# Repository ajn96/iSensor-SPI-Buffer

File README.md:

# iSensor SPI Buffer
The iSensor SPI Buffer is a hardware and software solution designed to buffer iSensor IMU data, enabling asynchronous sampling systems (specifically embedded Linux systems) such as the Raspberry Pi, BeagleBone, Nvidia Jetson, etc. to capture IMU data at high sampling rates **with accurate timestamps and** **without data loss**. Output data is provided through a USB Virtual COM port and/or a user SPI port allowing transparent augmentation of an existing IMU interface system.

The firmware runs on an STM32F303 microprocessor to enable full-throughput, buffered IMU data capture with a variety of output data formats. An ADG1611 analog switch IC to enable routing SYNC and DATA READY signals from the host system directly to the IMU. The SPI buffer board is designed to be compatible with all current and future iSensor IMU products. 

A custom PCB was designed to fit the profile and form factor of an ADIS1649x IMU. This profile allows the iSensor SPI Buffer to act as a drop-in solution for existing, high-performance solutions. The buffer interface is designed to mimic the iSensor page convention and SPI settings out-of-the box. 

Additional hardware and software resources are linked below.

[Detailed Register Map](markdown/REGISTER_DEFINITION.md)

[USB CLI Definition](markdown/USB_CLI.md)

[Python USB Interfacing Library](PythonUtil/)

[SD Card Data Logging Scripts](markdown/SD_SCRIPTS.md)

[Firmware Documentation (Doxygen)](https://ajn96.github.io/iSensor-SPI-Buffer/files.html)

[Software Timing Characterization](markdown/TIMING.MD)

[STM32 Processor Pin Map](markdown/PIN_MAP.md)

[Programming Guide](markdown/BUILDING.md)

A video walkthrough and tutorial of the SPI Buffer Board's features is hosted on YouTube. Click on the image below to check it out!

## Hardware Platform

This firmware is designed to operate in the STMicro processor family - specifically the STM32F303 processor. The STM32F303RET6 variant of the processor family was chosen for this application because of its large SRAM and low cost. 

Revision B of the PCB design includes the following features:

- STM32F303RET6 processor (64k SRAM, hardware SPI peripherals, DMA fabric)
- ADG1611 analog switch - used for mapping SYNC and DATA READY signals from the IMU to the buffer board or SPI host
- ADP1706 high-transient linear regulator - used to regulate USB 5V and power both the IMU and buffer board
  - Power supply selection jumper for powering the buffer board & IMU from the 24-pin IMU connector or USB
- USB C expansion port - Provides a USB virtual COM port command line interface to read/write registers and stream IMU data
- SD card slot - Allows IMU data to be captured "headless" without the use of a PC or SPI host
- LEDs - used to indicate buffer state and SPI buffer errors
- 24-pin IMU connectors - used to interface with and pass through IMU and SPI Buffer data to and from a host using SPI
- ADIS1650x footprint - used to enable the evaluation and use of compact iSensor IMUs

The iSensor SPI Buffer was designed to sit between an iSensor IMU and the SPI host without changing any existing PCB designs. 

## Development Environment and Hardware

### Software / IDE

The code contained in this repository was developed using the freely available [STM32 Cube IDE](https://my.st.com/content/my_st_com/en/products/development-tools/software-development-tools/stm32-software-development-tools/stm32-ides/stm32cubeide). A compatible project file is also included in this repository to make getting stared as easy as possible. 

### Hardware

A [TC2030-IDC cable](https://www.tag-connect.com/product/tc2030-idc-6-pin-tag-connect-plug-of-nails-spring-pin-cable-with-legs) must be used to interface with the SWD pads on the Rev B PCB. Development was originally done on an [NUCLEO-F303RE](https://www.st.com/en/evaluation-tools/nucleo-f303re.html) development board. When programming a buffer board, we've continued to use the NUCLEO as the SWD programmer. 

## Linux Driver Support

Support for the SPI Buffer Board in Linux (over SPI) was developed by [spalani7](https://github.com/spalani7). His repository is located  [here](https://github.com/spalani7/adi_imu_driver). For USB interfacing, the included Python library can be utilized for easy integration with any USB capable system.

## Design Requirements and Features

### IMU Register Interface

* "Invisible" SPI pass-through to an iSensor IMU, including modules that implement register pages
* iSensor-SPI-Buffer configuration registers and buffered data acquisition registers will be placed on unassigned IMU pages (Pages 253 - 255)

### Buffered Data Acquisition

* Autonomous IMU data acquisition will be driven by the IMU-generated data ready signal. Data will be stored in the iSensor-SPI-Buffer SRAM until retrieved by a user
* Programmable data request message (MOSI) to be transmitted after each data ready signal. Allows users to customize the register writes, contents, and order
* Programmable data acquisition length after each IMU data ready signal. Allows the user to configure the length of data read back from the IMU
* Programmable data acquisition SPI word size. The default 16-bit length provides support standard register reads, writes, and burst reads on most IMUs

### Configuration Options

* Buffer overflow setting (stop sampling vs delete oldest)
* Data ready input (from IMU) DIO number
* IMU Data ready trigger polarity
* Master SPI (interface between the iSensor-SPI-Buffer firmware and the IMU) 
  * SCLK Frequency
  * Stall time
* Slave SPI (interface between the iSensor-SPI-Buffer firmware and the host processor) 
  * Standard SPI settings (CPOL, CPHA, endianness)

### Buffer Design

* Reading a buffer retrieve register will dequeue data from the buffer data structure to the buffer output registers for retrieval by a user
* The user will can clear the buffer using a control register
* A buffer counter will be added to each buffer for the user to keep track of the state of the buffer. This counter must also be accessible without dequeuing data from buffer
* Using a maximum buffer entry size of 64 bytes, the buffer will provide a minimum of 512 frames of buffering using 32KB SRAM
  * STM32F303 has 80KB of SRAM available, so more than 512 entries may be feasible

## Architecture

### SPI Ports

The iSensor-SPI-Buffer firmware will utilize two hardware SPI ports. One operating as a master (SPI buffer to IMU communication) and the other as a slave (SPI buffer to host)
* The slave SPI port will expose the IMU register interface along with the iSensor-SPI-Buffer configuration registers to the master
* The slave SPI port will support all standard SPI configuration parameters
* The master SPI port will communicate with the IMU using the standard, iSensor SPI protocol
* The master SPI port configuration will be limited to customizing SCLK frequency and stall time

### Program Flow

The iSensor-SPI-Buffer communications interfaces (SPI, SD card logging, USB CLI) are interrupt driven. A main cyclic executive loop handles command execution, interrupt generation, and diagnostics. The cyclic executive flow is shown below:

**User SPI Interrupt**

There will be an ISR to handle user-initiated SPI transactions (slave interface). If the active register page is not one of the SPI buffer pages (253 - 255) all SPI transactions will be forwarded to the IMU downstream. 

SPI transactions will be classified as "read" or "write" by the SPI buffer board the same as the iSensor IMU SPI protocol. A write operation is signaled by setting the MSB of each 16-bit word. The upper 8 bits of the 16-bit transaction contain the register address to be written to as well as the read/write bit. The lower 8 bits of the 16-bit transaction contain the data to be written. 

A single read request transmitted to the SPI buffer on the slave interface will result in *two* SPI transactions sent to the IMU on the master interface. The first transaction sends the register read request to the IMU and the second reads the requested register contents data back from the IMU. The requested IMU register is then loaded into the SPI buffer user SPI transmit buffer so that it is available to the user on the next user SPI transaction.  For write transactions, a single write command will be sent to the IMU. The data resulting from the write transaction is then loaded into the SPI buffer user SPI transmit buffer. Unlike the read operation, a write operation will not automatically generate an additional SPI transaction. The diagram below shows the IMU SPI pass-through process for a register read operation.

**Autonomous Data Capture**

When the currently selected page is 255 (buffer output register page), the iSensor SPI Buffer firmware will begin to monitor a user-specified GPIO interrupt for data ready signals pulses. Once a data ready pulse is detected, the firmware will transmit the data contained in page 254 (buffer transmit data) in the order specified by the user. Data received from the IMU during each 16-bit transaction will be stored in a new buffer entry in the iSensor-SPI-Buffer SRAM. The firmware will use DMA and timer peripherals to perform the SPI transactions with minimal CPU intervention while giving control over the SPI SCLK and stall time. 

The data capture ISR will be triggered by a user-specified GPIO, corresponding to the IMU data ready signal. The data capture ISR will configure a timer peripheral (which drives SPI word transmission timing) to trigger a DMA between memory and SPI. A DMA done ISR will handle cleaning up the DMA transactions and incrementing buffer pointers following a complete data set acquisition from the IMU. If the selected page is changed off page 255, the IMU data ready interrupt data capture functionality will be disabled (can be re-enabled by writing 255 to the page ID register on any page).

**User Interrupt Signaling (to host)**

Each of the four DIO lines from the iSensor-SPI-Buffer to the master device can be configured to operate in one of four modes
* Watermark Interrupt Mode: The selected DIO will go high when a specified number of samples are available to be dequeued. This allows a master device to simply monitor the data ready interrupt signal for a positive edge, and then dequeue a large number of IMU data samples
* Buffer Full Interrupt Mode: The selected DIO will go high when the buffer is full
* Error Interrupt Mode: The selected DIO will go high when an error is detected and flagged in the STATUS register
* Pin Pass-Through Mode: The DIO output from the IMU (e.g. a data ready signal or sync signal) will be directly connected to the master device, using an ADG1611 switch. When a DIO is configured in pin pass-through mode it cannot be used for interrupt signaling

The state of each interrupt signal is checked and updated on each iteration of the main cyclic executive loop. This ensures quick response time to changes in the buffer state while maintaining a simple program flow.

**Command Execution**

* When a write is issued the USER_COMMAND register, a COMMAND flag will be set and processed by the cyclic executive loop
* While a command is being executed, the user SPI port will be disabled, and any interrupt lines (data ready or buffer full) will be brought low

### Register Interface

* Configuration registers for iSensor SPI buffer available on page 253
* The data acquisition write data registers (data to transmit per data ready) available on page 254
* Buffer output data registers on page 255
* Volatile output registers available on page 252

## Recovering From a Bad SPI Configuration

This buffer firmware includes a feature that allows the host SPI peripheral on the buffer board to be reconfigured to suit the host's needs. Because of this, it's possible to lock yourself out of the buffer board. A bad SPI configuration will usually look like the buffer board is returning the same value repeatedly for all registers. Note that the buffer board returning 0xFFFF or 0x0000 could be caused by other issues (no power to the buffer board, bad connection to the IMU, etc.) A bad SPI configuration will look similar to the image below.

Recovering from a bad configuration requires using the USB CLI to communicate with the buffer board's firmware. While not mandatory, we recommend changing the jumper on the buffer board to USB power mode. The jumper just needs to be repositioned as shown below. 

Using a terminal program such as [TeraTerm](https://ttssh2.osdn.jp/index.html.en) or [PuTTY](https://www.chiark.greenend.org.uk/~sgtatham/putty/) in Windows, connect to the board using the enumerated COM port. The virtual USB port will automatically detect the host serial settings, so additional configuration is usually unnecessary. 

Once connected to the CLI, you can verify that the board is communicating correctly by typing `help` into the console. You should see a message like the one shown below.

After you've verified that the CLI is working correctly, type the following command, followed by a carriage return.

`freset`

This will execute a factory reset command followed by a flash update command. The board should now be reset to SPI Mode 3 with CS active low. The default register settings will have also been committed to flash, so they should persist throughout reboots. 

"The SPI who loved me" - PK

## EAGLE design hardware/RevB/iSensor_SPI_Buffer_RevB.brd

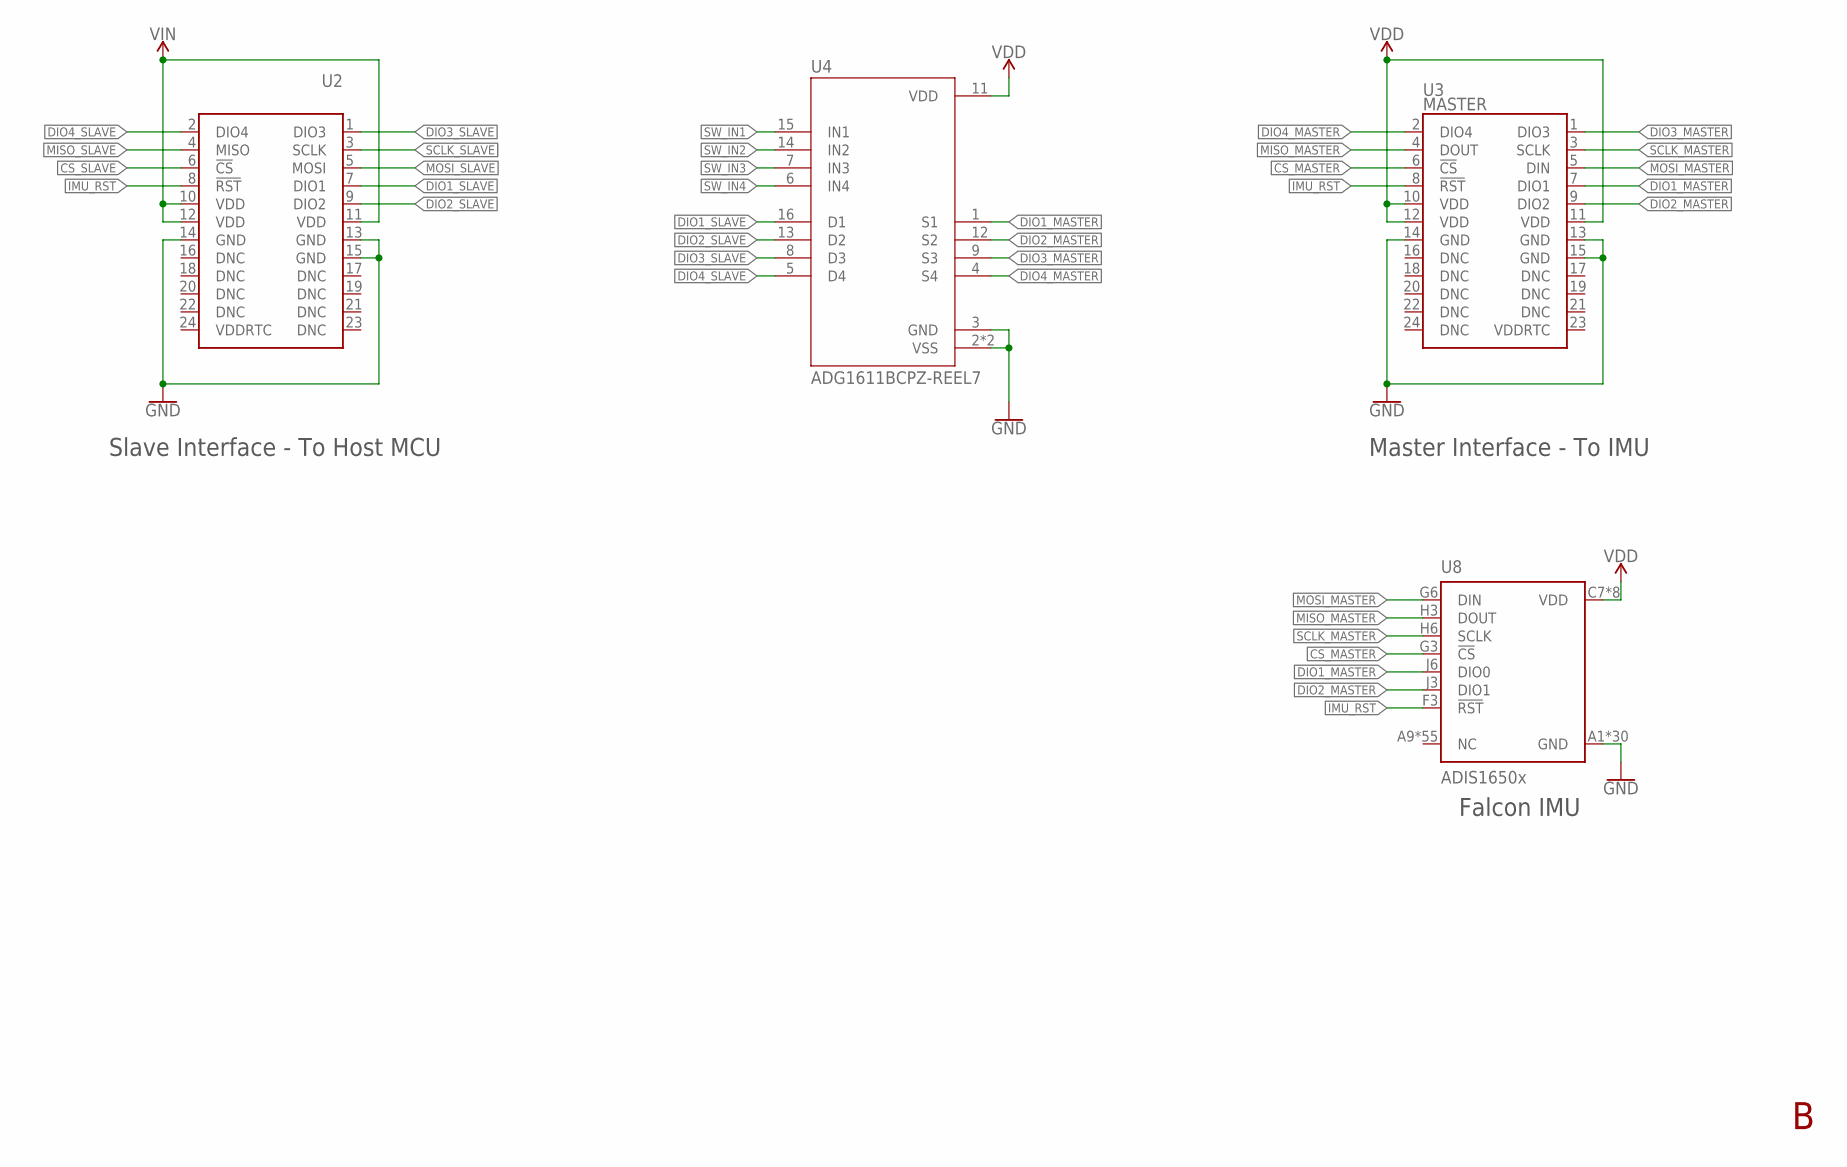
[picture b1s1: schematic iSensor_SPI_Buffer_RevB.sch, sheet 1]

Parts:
U2: MW-12-03-H-D-130-112
U3: MASTER; ADIS1648X
U4: ADG1611BCPZ-REEL7; QFN65P400X400X80-17N
U8: ADIS1650x; ADIS1650X

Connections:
CS_MASTER: U3.6 (!CS), U8.G3 (!CS); also elsewhere on the board
CS_SLAVE: U2.6 (!CS); also elsewhere on the board
DIO1_MASTER: U3.7 (DIO1), U4.1 (S1), U8.J6 (DIO0); also elsewhere on the board
DIO1_SLAVE: U2.7 (DIO1), U4.16 (D1); also elsewhere on the board
DIO2_MASTER: U3.9 (DIO2), U4.12 (S2), U8.J3 (DIO1); also elsewhere on the board
DIO2_SLAVE: U2.9 (DIO2), U4.13 (D2); also elsewhere on the board
DIO3_MASTER: U3.1 (DIO3), U4.9 (S3); also elsewhere on the board
DIO3_SLAVE: U2.1 (DIO3), U4.8 (D3); also elsewhere on the board
DIO4_MASTER: U3.2 (DIO4), U4.4 (S4); also elsewhere on the board
DIO4_SLAVE: U2.2 (DIO4), U4.5 (D4); also elsewhere on the board
GND: U2.13 (GND), U2.14 (GND), U2.15 (GND), U3.13 (GND), U3.14 (GND), U3.15 (GND), U4.2 (VSS), U4.3 (GND), U4.17 (VSS), U8.A1 (GND), U8.A2 (GND), U8.A3 (GND), U8.A4 (GND), U8.A5 (GND), U8.A6 (GND), U8.A7 (GND), U8.A8 (GND), U8.B3 (GND), U8.B4 (GND), U8.B5 (GND), U8.B6 (GND), U8.C2 (GND), U8.C6 (GND), U8.D3 (GND), U8.E2 (GND), U8.E6 (GND), U8.E7 (GND), U8.F1 (GND), U8.F5 (GND), U8.F6 (GND), U8.F8 (GND), U8.G2 (GND), U8.G7 (GND), U8.H8 (GND), U8.J2 (GND), U8.J7 (GND), U8.K1 (GND), U8.K3 (GND), U8.K8 (GND); also elsewhere on the board
IMU_RST: U2.8 (!RST), U3.8 (!RST), U8.F3 (!RST)
MISO_MASTER: U3.4 (DOUT), U8.H3 (DOUT); also elsewhere on the board
MISO_SLAVE: U2.4 (MISO); also elsewhere on the board
MOSI_MASTER: U3.5 (DIN), U8.G6 (DIN); also elsewhere on the board
MOSI_SLAVE: U2.5 (MOSI); also elsewhere on the board
SCLK_MASTER: U3.3 (SCLK), U8.H6 (SCLK); also elsewhere on the board
SCLK_SLAVE: U2.3 (SCLK); also elsewhere on the board
SW_IN1: U4.15 (IN1); also elsewhere on the board
SW_IN2: U4.14 (IN2); also elsewhere on the board
SW_IN3: U4.7 (IN3); also elsewhere on the board
SW_IN4: U4.6 (IN4); also elsewhere on the board
VDD: U3.10 (VDD), U3.11 (VDD), U3.12 (VDD), U4.11 (VDD), U8.C7 (VDD), U8.D6 (VDD), U8.E3 (VDD), U8.G1 (VDD), U8.H1 (VDD), U8.J4 (VDD), U8.J5 (VDD), U8.K6 (VDD); also elsewhere on the board
VIN: U2.10 (VDD), U2.11 (VDD), U2.12 (VDD); also elsewhere on the board

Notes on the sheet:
Slave Interface - To Host MCU
Master Interface - To IMU
Falcon IMU

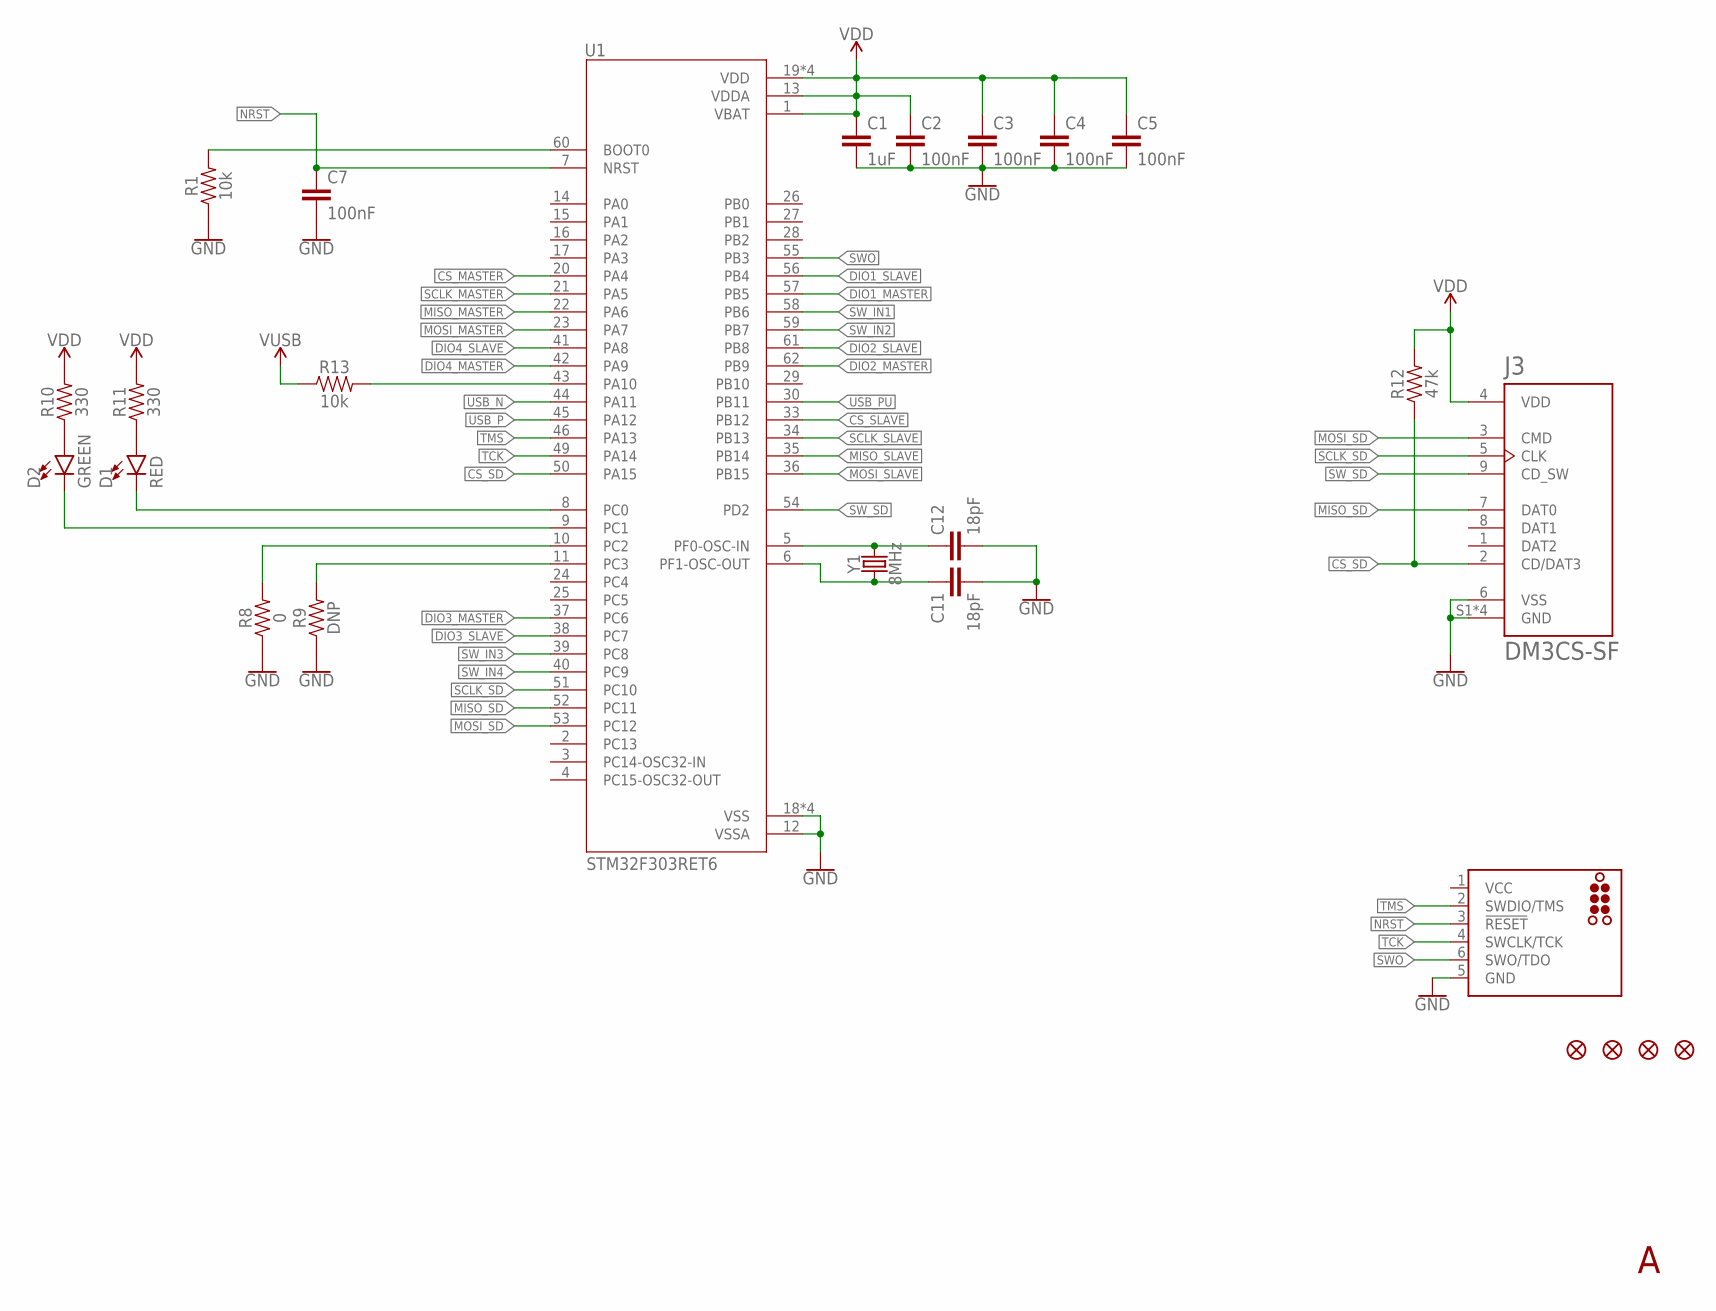
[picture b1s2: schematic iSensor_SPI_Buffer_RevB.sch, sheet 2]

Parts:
C1: 1uF; 0603
C2, C3, C4, C5, C7: 100nF; 0603
C11, C12: 18pF; 0402
D1: RED; LED-0603
D2: GREEN; LED-0603
FD1, FD2, FD3, FD4: FIDUCIAL1X2; FIDUCIAL-1X2
J1: TC2030_SWD-MCP; TC2030-MCP
J3: DM3CS-SF; HRS_DM3CS-SF
R1, R13: 10k; 0402
R8: 0; 0402
R9: DNP; 0402
R10, R11: 330; 0402
R12: 47k; 0402
U1: STM32F303RET6; QFP50P1200X1200X160-64N
Y1: 8MHz; CRYSTAL-SMD-5X3.2-4PAD

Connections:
CS_MASTER: U1.20 (PA4); also elsewhere on the board
CS_SD: J3.2 (CD/DAT3), R12.1, U1.50 (PA15)
CS_SLAVE: U1.33 (PB12); also elsewhere on the board
DIO1_MASTER: U1.57 (PB5); also elsewhere on the board
DIO1_SLAVE: U1.56 (PB4); also elsewhere on the board
DIO2_MASTER: U1.62 (PB9); also elsewhere on the board
DIO2_SLAVE: U1.61 (PB8); also elsewhere on the board
DIO3_MASTER: U1.37 (PC6); also elsewhere on the board
DIO3_SLAVE: U1.38 (PC7); also elsewhere on the board
DIO4_MASTER: U1.42 (PA9); also elsewhere on the board
DIO4_SLAVE: U1.41 (PA8); also elsewhere on the board
GND: C1.2, C2.2, C3.2, C4.2, C5.2, C7.2, C11.2, C12.2, J1.5 (GND), J3.6 (VSS), J3.S1 (GND), J3.S2 (GND), J3.S3 (GND), J3.S5 (GND), R1.1, R8.1, R9.1, U1.12 (VSSA), U1.18 (VSS), U1.31 (VSS), U1.47 (VSS), U1.63 (VSS); also elsewhere on the board
MISO_MASTER: U1.22 (PA6); also elsewhere on the board
MISO_SD: J3.7 (DAT0), U1.52 (PC11)
MISO_SLAVE: U1.35 (PB14); also elsewhere on the board
MOSI_MASTER: U1.23 (PA7); also elsewhere on the board
MOSI_SD: J3.3 (CMD), U1.53 (PC12)
MOSI_SLAVE: U1.36 (PB15); also elsewhere on the board
unnamed: R1.2, U1.60 (BOOT0)
unnamed: D1.C, U1.8 (PC0)
unnamed: D2.C, U1.9 (PC1)
unnamed: R8.2, U1.10 (PC2)
unnamed: R9.2, U1.11 (PC3)
unnamed: D2.A, R10.1
unnamed: D1.A, R11.1
unnamed: R13.2, U1.43 (PA10)
unnamed: C11.1, U1.6 (PF1-OSC-OUT), Y1.1
unnamed: C12.1, U1.5 (PF0-OSC-IN), Y1.3 (2)
NRST: C7.1, J1.3 (!RESET), U1.7 (NRST)
SCLK_MASTER: U1.21 (PA5); also elsewhere on the board
SCLK_SD: J3.5 (CLK), U1.51 (PC10)
SCLK_SLAVE: U1.34 (PB13); also elsewhere on the board
SWO: J1.6 (SWO/TDO), U1.55 (PB3)
SW_IN1: U1.58 (PB6); also elsewhere on the board
SW_IN2: U1.59 (PB7); also elsewhere on the board
SW_IN3: U1.39 (PC8); also elsewhere on the board
SW_IN4: U1.40 (PC9); also elsewhere on the board
SW_SD: J3.9 (CD_SW), U1.54 (PD2)
TCK: J1.4 (SWCLK/TCK), U1.49 (PA14)
TMS: J1.2 (SWDIO/TMS), U1.46 (PA13)
USB_N: U1.44 (PA11); also elsewhere on the board
USB_P: U1.45 (PA12); also elsewhere on the board
USB_PU: U1.30 (PB11); also elsewhere on the board
VDD: C1.1, C2.1, C3.1, C4.1, C5.1, J3.4 (VDD), R10.2, R11.2, R12.2, U1.1 (VBAT), U1.13 (VDDA), U1.19 (VDD), U1.32 (VDD), U1.48 (VDD), U1.64 (VDD); also elsewhere on the board
V_USB: R13.1; also elsewhere on the board

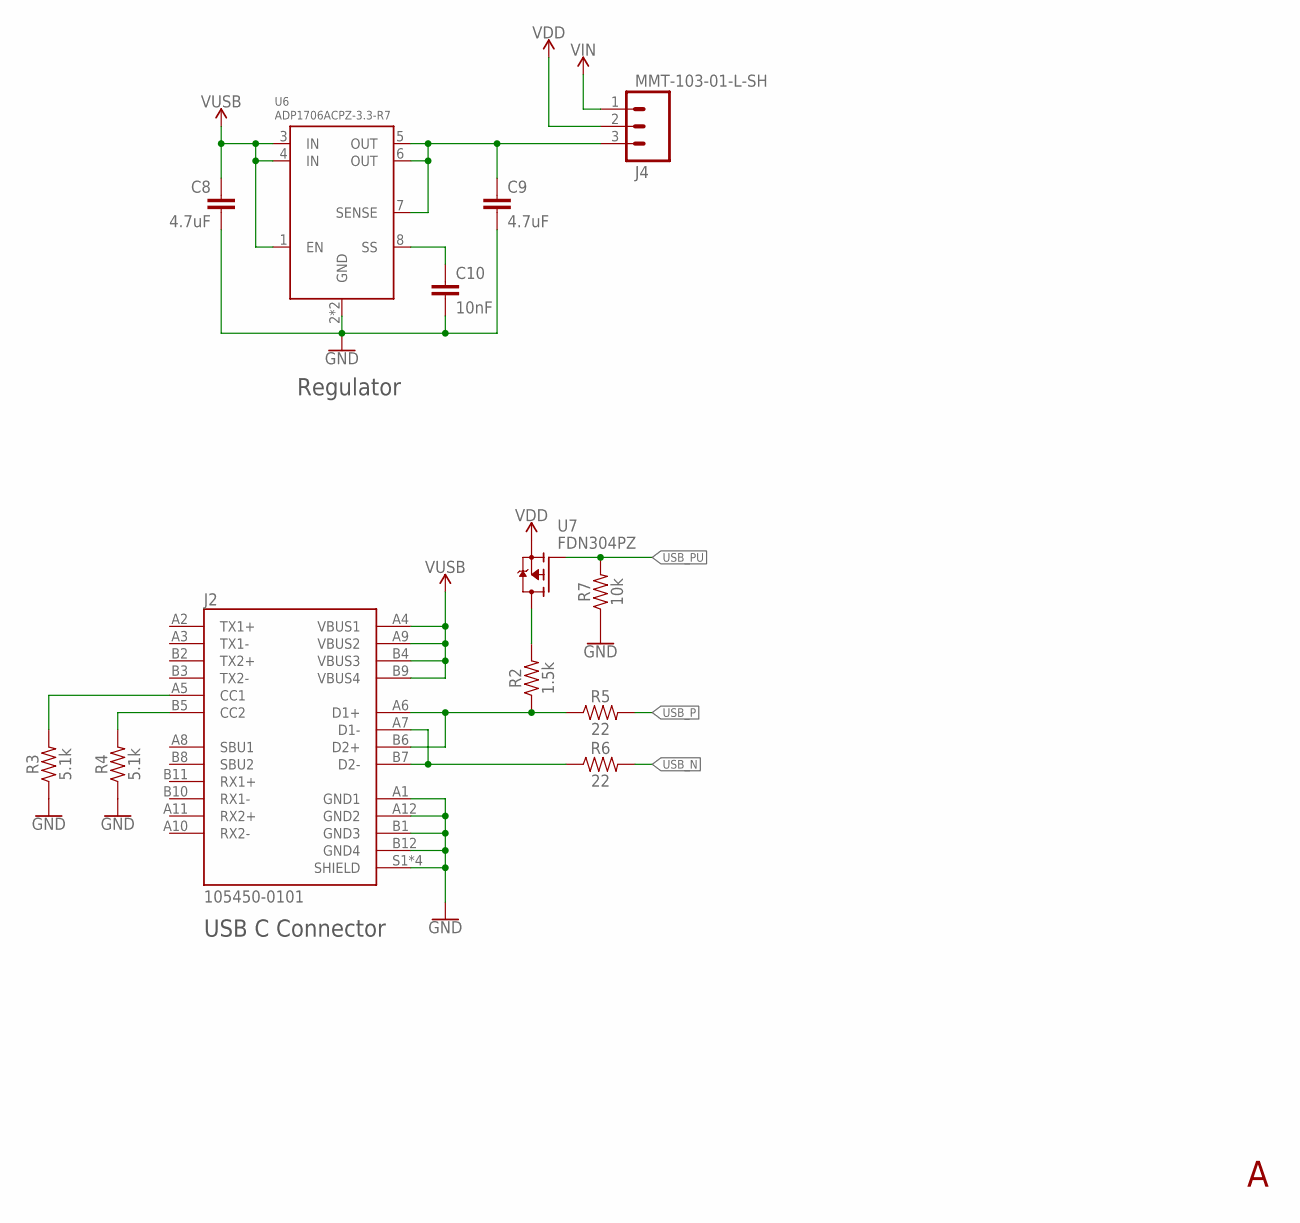
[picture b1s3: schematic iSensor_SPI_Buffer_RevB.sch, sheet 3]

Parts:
C8, C9: 4.7uF; 0805
C10: 10nF; 0603
J2: 105450-0101; MOLEX_105450-0101
J4: MMT-103-01-L-SH; SAMTEC-MMT-103-01-X-SH
R2: 1.5k; 0402
R3, R4: 5.1k; 0402
R5, R6: 22; 0402
R7: 10k; 0402
U6: ADP1706ACPZ-3.3-R7; DFN300X300X90-9N
U7: FDN304PZ; SOT23

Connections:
GND: C8.2, C9.2, C10.2, J2.A1 (GND1), J2.A12 (GND2), J2.B1 (GND3), J2.B12 (GND4), J2.S1 (SHIELD), J2.S2 (SHIELD), J2.S3 (SHIELD), J2.S4 (SHIELD), R3.1, R4.1, R7.1, U6.2 (GND), U6.9 (GND); also elsewhere on the board
unnamed: J2.A5 (CC1), R3.2
unnamed: J2.B5 (CC2), R4.2
unnamed: C9.1, J4.3, U6.5 (OUT), U6.6 (OUT), U6.7 (SENSE)
unnamed: R2.2, U7.3 (D)
unnamed: C10.1, U6.8 (SS)
USB+_N: J2.A7 (D1-), J2.B7 (D2-), R6.1
USB+_P: J2.A6 (D1+), J2.B6 (D2+), R2.1, R5.1
USB_N: R6.2; also elsewhere on the board
USB_P: R5.2; also elsewhere on the board
USB_PU: R7.2, U7.1 (G); also elsewhere on the board
VDD: J4.2, U7.2 (S); also elsewhere on the board
VIN: J4.1; also elsewhere on the board
V_USB: C8.1, J2.A4 (VBUS1), J2.A9 (VBUS2), J2.B4 (VBUS3), J2.B9 (VBUS4), U6.1 (EN), U6.3 (IN), U6.4 (IN); also elsewhere on the board

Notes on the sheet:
USB C Connector
Regulator

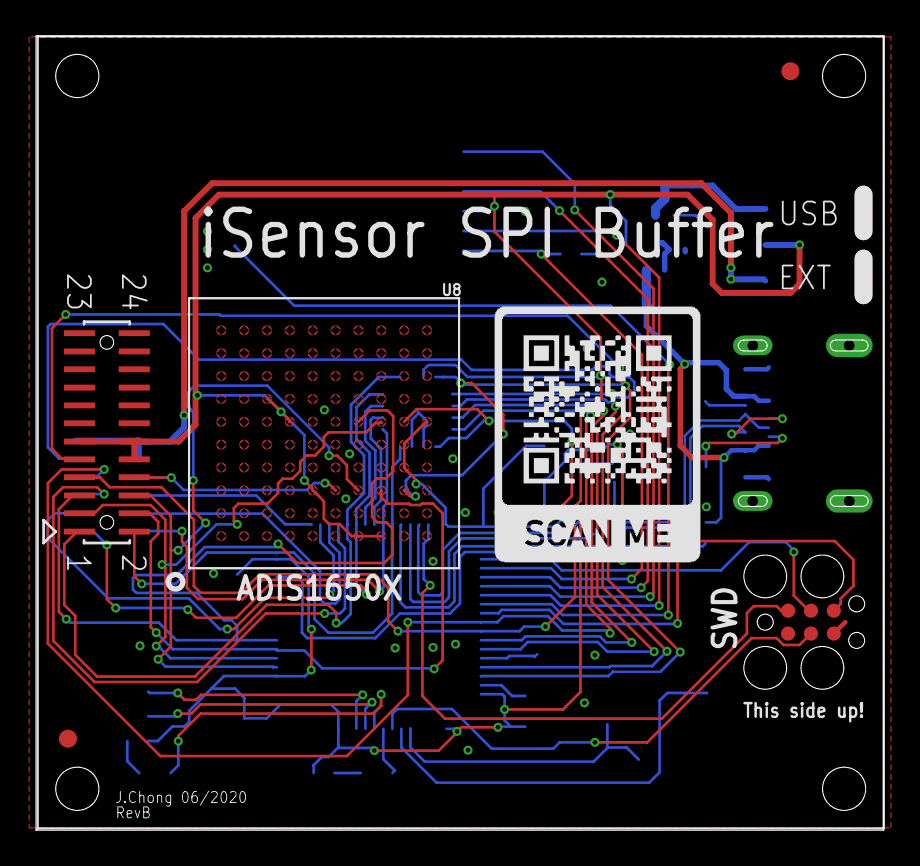
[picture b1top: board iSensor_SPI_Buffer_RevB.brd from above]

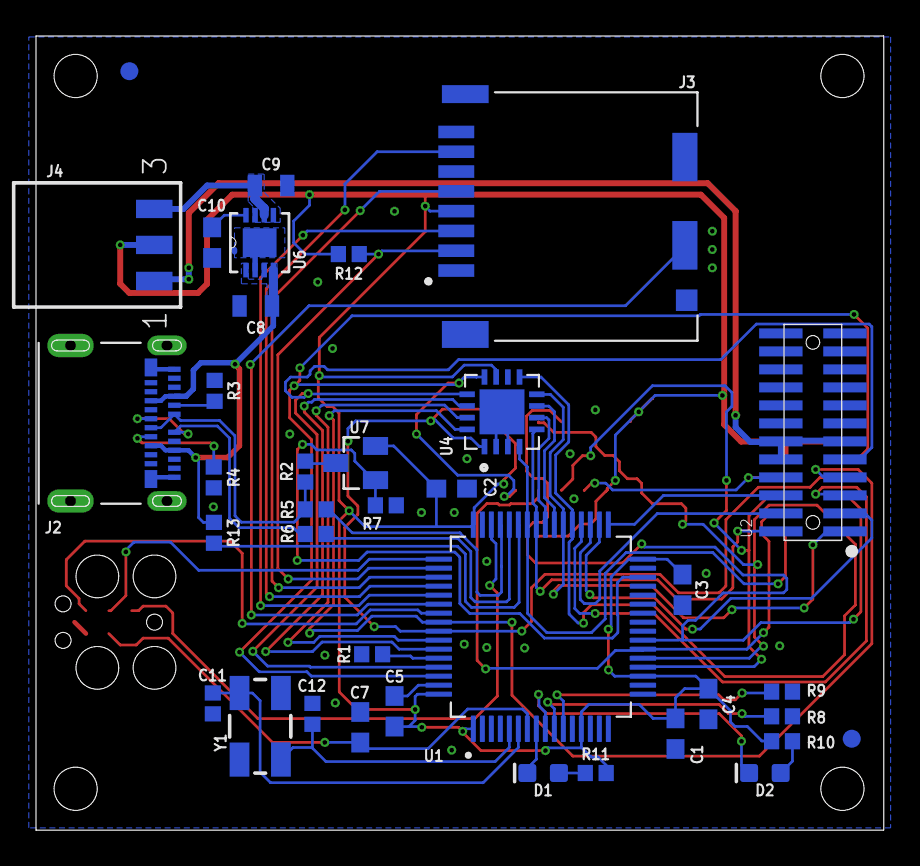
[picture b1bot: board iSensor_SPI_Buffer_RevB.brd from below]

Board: 2 copper layers, 47.1 x 44.1 mm, 42 parts (37 on the bottom side), 54 nets.

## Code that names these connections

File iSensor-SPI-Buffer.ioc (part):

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Mcu.Name=STM32F303R(D-E)Tx
Mcu.Package=LQFP64
Mcu.UserName=STM32F303RETx
PA11.Mode=Device
PA11.Signal=USB_DM
PA12.Mode=Device
PA12.Signal=USB_DP
PA13.Signal=SYS_JTMS-SWDIO
PA14.Signal=SYS_JTCK-SWCLK
PA15.Mode=NSS_Signal_Hard_Output
PA15.Signal=SPI3_NSS
PA4.Signal=S_TIM3_CH2
PA5.Mode=Full_Duplex_Master
PA5.Signal=SPI1_SCK
PA6.Mode=Full_Duplex_Master
PA6.Signal=SPI1_MISO
PA7.Mode=Full_Duplex_Master
PA7.Signal=SPI1_MOSI
PA8.Signal=GPIO_Output
PA9.Signal=GPIO_Input
PB12.Mode=NSS_Signal_Hard_Input
PB12.Signal=SPI2_NSS
PB13.Mode=Full_Duplex_Slave
PB13.Signal=SPI2_SCK
PB14.Mode=Full_Duplex_Slave
PB14.Signal=SPI2_MISO
PB15.Mode=Full_Duplex_Slave
PB15.Signal=SPI2_MOSI
PB3.Signal=SYS_JTDO-TRACESWO
PB4.Signal=GPIO_Output
PB5.Signal=GPXTI5
PB6.Signal=GPIO_Output
PB7.Signal=GPIO_Output
PB8.Signal=GPIO_Output
PB9.Signal=GPIO_Input
PC10.Mode=Full_Duplex_Master
PC10.Signal=SPI3_SCK
PC11.Mode=Full_Duplex_Master
PC11.Signal=SPI3_MISO
PC12.Mode=Full_Duplex_Master
PC12.Signal=SPI3_MOSI
PC6.Signal=GPIO_Input
PC7.Signal=GPIO_Output
PC8.Signal=GPIO_Output
PC9.Signal=GPIO_Output
RCC.HSE_VALUE=8000000
RCC.SYSCLKFreq_VALUE=72000000
RCC.SYSCLKSourceVirtual=RCC_SYSCLKSOURCE_PLLCLK
board=custom

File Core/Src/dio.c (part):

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		g_regs[SYNC_FREQ_REG] = 1;
	}

	/* Pin in question is PB8. Can mux to timer16, CH1. */

	/**TIM16 GPIO Configuration PB8 */
	GPIO_InitStruct.Pin = GPIO_PIN_8;
	GPIO_InitStruct.Mode = GPIO_MODE_AF_PP;
	GPIO_InitStruct.Pull = GPIO_NOPULL;
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	GPIO_InitStruct.Pull = GPIO_NOPULL;
	GPIO_InitStruct.Speed = GPIO_SPEED_FREQ_HIGH;

	/* DIO1 master (PB5) */
	HAL_GPIO_DeInit(GPIOB, GPIO_PIN_5);
	GPIO_InitStruct.Pin = GPIO_PIN_5;
	if(config & 0x1)
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	/* Apply settings */
	HAL_GPIO_Init(GPIOB, &GPIO_InitStruct);

	/* DIO2 master (PB9) */
	HAL_GPIO_DeInit(GPIOB, GPIO_PIN_9);
	GPIO_InitStruct.Pin = GPIO_PIN_9;
	if(config & 0x2)
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	/* Apply settings */
	HAL_GPIO_Init(GPIOB, &GPIO_InitStruct);

	/* DIO3 master (PC6) */
	HAL_GPIO_DeInit(GPIOC, GPIO_PIN_6);
	GPIO_InitStruct.Pin = GPIO_PIN_6;
	if(config & 0x4)
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	/* Apply settings */
	HAL_GPIO_Init(GPIOC, &GPIO_InitStruct);

	/* DIO4 master (PA9) */
	HAL_GPIO_DeInit(GPIOA, GPIO_PIN_9);
	GPIO_InitStruct.Pin = GPIO_PIN_9;
	if(config & 0x8)
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  * General procedure is as follows:
  *
  * passPins
  * Set SW_IN1 - SW_IN4 output values based on passPins. These act as inputs
  * to the ADG1611 analog switch. For each bit set in passPins, configure the
  * corresponding DIOx_Slave signal as an input (tristate). Only perform this
  * configuration if the pin is not currently acting as a PPS input
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
	/* All SW_INx pins are driven as outputs */

	/* SW_IN1 (PB6) */
	if(g_pinConfig.passPins & 0x1)
		GPIOB->ODR &= ~GPIO_PIN_6;
	else
		GPIOB->ODR |= GPIO_PIN_6;

	/* SW_IN2 (PB7) */
	if(g_pinConfig.passPins & 0x2)
		GPIOB->ODR &= ~GPIO_PIN_7;
	else
		GPIOB->ODR |= GPIO_PIN_7;

	/* SW_IN3 (PC8) */
	if(g_pinConfig.passPins & 0x4)
		GPIOC->ODR &= ~GPIO_PIN_8;
	else
		GPIOC->ODR |= GPIO_PIN_8;

	/* SW_IN4 (PC9) */
	if(g_pinConfig.passPins & 0x8)
		GPIOC->ODR &= ~GPIO_PIN_9;
	else
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
	/* For each DIOx_Slave pin, set as output if used as interrupt source. Set as input if used as pass pin (and not PPS) */

	/* DIO1_Slave (PB4) */
	if((g_pinConfig.watermarkPins & 0x1) || (g_pinConfig.overflowPins & 0x1) || (g_pinConfig.errorPins & 0x1))
	{
		HAL_GPIO_DeInit(GPIOB, GPIO_PIN_4);
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		HAL_GPIO_Init(GPIOB, &GPIO_InitStruct);
	}

	/* DIO2_Slave (PB8) */
	if((g_pinConfig.watermarkPins & 0x2) || (g_pinConfig.overflowPins & 0x2) || (g_pinConfig.errorPins & 0x2))
	{
		HAL_GPIO_DeInit(GPIOB, GPIO_PIN_8);
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		HAL_GPIO_Init(GPIOB, &GPIO_InitStruct);
	}

	/* DIO3_Slave (PC7) */
	if((g_pinConfig.watermarkPins & 0x4) || (g_pinConfig.overflowPins & 0x4) || (g_pinConfig.errorPins & 0x4))
	{
		GPIO_InitStruct.Mode = GPIO_MODE_OUTPUT_PP;
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		HAL_GPIO_Init(GPIOC, &GPIO_InitStruct);
	}

	/* DIO4_Slave (PA8) */
	if((g_pinConfig.watermarkPins & 0x8) || (g_pinConfig.overflowPins & 0x8) || (g_pinConfig.errorPins & 0x8))
	{
		HAL_GPIO_DeInit(GPIOA, GPIO_PIN_8);
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
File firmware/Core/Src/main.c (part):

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	/*Configure GPIO port C pin Output Level */
	HAL_GPIO_WritePin(GPIOC, GPIO_PIN_0|GPIO_PIN_1|GPIO_PIN_8|GPIO_PIN_9, GPIO_PIN_RESET);

	/*Configure GPIO port A input pin : PA8 PA9 */
	GPIO_InitStruct.Pin = GPIO_PIN_8|GPIO_PIN_9;
	GPIO_InitStruct.Mode = GPIO_MODE_INPUT;
	GPIO_InitStruct.Pull = GPIO_NOPULL;
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	GPIO_InitStruct.Speed = GPIO_SPEED_FREQ_HIGH;
	HAL_GPIO_Init(GPIOB, &GPIO_InitStruct);

	/*Configure GPIO port B input pins : PB4 PB5 PB8 PB9 */
	GPIO_InitStruct.Pin = GPIO_PIN_4|GPIO_PIN_5|GPIO_PIN_8|GPIO_PIN_9;
	GPIO_InitStruct.Mode = GPIO_MODE_INPUT;
	GPIO_InitStruct.Pull = GPIO_NOPULL;
	HAL_GPIO_Init(GPIOB, &GPIO_InitStruct);

	/*Configure GPIO port B output pins : PB6 PB7 (Switch control) */
	GPIO_InitStruct.Pin = GPIO_PIN_6|GPIO_PIN_7;
	GPIO_InitStruct.Mode = GPIO_MODE_OUTPUT_PP;
	GPIO_InitStruct.Pull = GPIO_NOPULL;
	GPIO_InitStruct.Speed = GPIO_SPEED_FREQ_HIGH;
	HAL_GPIO_Init(GPIOB, &GPIO_InitStruct);

	/*Configure GPIO port C input pins : PC2 PC3 PC6 PC7 */
	GPIO_InitStruct.Pin = GPIO_PIN_2|GPIO_PIN_3|GPIO_PIN_6|GPIO_PIN_7;
	GPIO_InitStruct.Mode = GPIO_MODE_INPUT;
	GPIO_InitStruct.Pull = GPIO_NOPULL;
	HAL_GPIO_Init(GPIOC, &GPIO_InitStruct);

	/*Configure GPIO port C output pins : PC0 PC1 PC8 PC9 (LED, Switch control) */
	GPIO_InitStruct.Pin = GPIO_PIN_0|GPIO_PIN_1|GPIO_PIN_8|GPIO_PIN_9;
	GPIO_InitStruct.Mode = GPIO_MODE_OUTPUT_PP;
	GPIO_InitStruct.Pull = GPIO_NOPULL;
	GPIO_InitStruct.Speed = GPIO_SPEED_FREQ_HIGH;
	HAL_GPIO_Init(GPIOC, &GPIO_InitStruct);

	/**TIM3 GPIO Configuration PA4     ------> TIM3_CH2 */
	GPIO_InitStruct.Pin = GPIO_PIN_4;
	GPIO_InitStruct.Mode = GPIO_MODE_AF_PP;
	GPIO_InitStruct.Pull = GPIO_NOPULL;
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	GPIO_InitStruct.Alternate = GPIO_AF2_TIM3;
	HAL_GPIO_Init(GPIOA, &GPIO_InitStruct);

	/*Configure GPIO port D input pins : PD2 (SD card detect) */
	GPIO_InitStruct.Pin = GPIO_PIN_2;
	GPIO_InitStruct.Mode = GPIO_MODE_INPUT;
	GPIO_InitStruct.Pull = GPIO_NOPULL;
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
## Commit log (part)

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2020-06-27 Renamed register array to g_regs. Starting to refactor to work on variable scope
2020-06-27 More refactoring and cleanup on coding style. Renamed imu_passthrough module to imu spi to be more concise
2020-06-27 Rebuilt firmware documentation
2020-06-27 Reordered status bits
2020-06-27 Updated project file
2020-06-27 Added missing variable reference
2020-06-29 Started CLI implementation
2020-06-29 Implemented basic CLI. Read/write/help working
2020-07-01 Added docs for USB_CONFIG register
2020-07-01 Made it so delim char does not appear on end of line
2020-07-01 Added pictures to USB cli definition
2020-07-05 Updated register info
2020-07-06 Updated CLI images
2020-07-06 Updated regmaps with new registers
2020-07-06 Added UTC timestamp to buffer entry. Removed delta time
2020-07-06 Changed timestamps to be written to buffer word wise
2020-07-06 Fixed buf data base address define
2020-07-06 Updated gitignore
2020-07-06 Command echo is now blocking. Might do something more efficient later
2020-07-07 Fixed bug where LSB first mode wouldnt actually change
2020-07-07 Marked command as volatile
2020-07-07 Added more commenting for missing documentation
2020-07-07 Changed firmware rev to 1.01
2020-07-07 Added generated init code for IMU DMA
2020-07-07 removed unneeded global flags for active interrupt masks
2020-07-07 Started logic for IMU burst data capture
2020-07-09 Changed rev back to 1.0 for re-release
2020-07-09 Changed firmware rev back to 1.1
2020-07-09 Fixed buf_config default, removed status TC test
2020-07-09 Updated the readme to include instructions on changing the spi settings using the USB cli and added a link to the Linux driver repository
2020-07-10 Added bit to USB_CONFIG which allows a user to disable the CLI echo. This is useful when programatically interfacing with Spi buffer CLI (don't have to throw away echoed commands)
2020-07-10 Changed reset command to a factory reset command, freset
2020-07-10 Added HAL code for ADC
2020-07-10 temp reading now produces and scales data. Think the wrong source is set, output values are way off
2020-07-13 Restructured main loop to allow better latency setting interrupts
2020-07-15 Fixed issue where you would sometimes get invalid IMU stall time
2020-07-20 Fixed typo
2020-07-21 Added temp register
2020-07-21 Started working on burst implementation
2020-07-22 Implemented IMU burst data streaming functionality using DMA
2020-07-23 Flush SPI when exiting burst
2020-07-23 Improved documentation for temp sensor module, added temp warning to STATUS
2020-07-23 Added burst regs to regmap
2020-07-24 Initial source commit for script module (USB + CLI)
2020-07-24 Changed firmware rev to 1.3
2020-07-24 Fixed register bit assignments to actually match docs
2020-07-24 Refactored script parse function to be a more maintainable
2020-07-27 Updated timestamp again with a higher sample freq
2020-07-27 Made it so FW_REV is loaded from #define instead of flash
2020-07-28 Reworked user SPI interface to interrupt on rising edge of CS in all modes
2020-07-28 added PPS unlock detection for pps period error of more than 1%
2020-07-28 Added more documentation, cleaned up variable scopes
2020-07-28 Incremented working version number
2020-07-28 Added SD card interface module stubs
2020-07-29 Fixed extra word being placed in SPI Tx FIFO when an overrun error event is generated
2020-07-29 Added handling for new commands
2020-07-29 Moved SPI3 init to SD card module, added outline of functionality
2020-07-29 Continued script execution engine implementation
2020-07-29 Added documentation for SD data logging
2020-08-02 Fixed issue with CS PWM timer configuration making changes take one period to be applied. Now compare register is updated immediately
2020-08-02 Added function to check script autorun. Moved watchdog flag check to after regs are loaded from flash (whoops)
2020-08-02 Changed init order slightly to make behavior more consistent
2020-08-02 Incremented working firmware rev to 1.5
2020-08-05 Updated capture running check to look at DMA count registers
2020-08-05 Added image showing SPI pass through
2020-08-05 Incremented working firmware rev
2020-08-06 Added call to errorhandler which was somehow removed
2020-08-06 Fixed issue where IMU data ready interrupt would be cleared by CS rising edge ISR. Fixed issue where sometimes user SPI would not properly reset before a burst, resulting in a data offset
2020-08-06 Changed working firmware rev to 1.7
2020-08-06 Added function to find vdd value from vrefint measurement
2020-08-07 Added docs for watermark strobe mode
2020-08-07 Updated formatting and regenerated output
2020-08-07 Added BUF_CNT output to burst word 0
2020-08-07 Changed working firmware rev to 1.8:
2020-08-09 Refactored script code to be context aware and just call appropriate USB/SD card handler for tx data. This simplifies handling multi-buffer writes
2020-08-09 Moved stream check to its own function within script module. Is called periodically in main loop
2020-08-10 USB CLI functionality now sits entirely on top of script module for all functionality
2020-08-10 Made functional minimum watermark level for streams 1
2020-08-10 Also masked lowest bit in address
2020-08-10 Fixed potential buffer overflow issue. Reworked blocking USB transmit function call
2020-08-23 Renamed ADC functions
2020-08-23 SD card logging implementation should be done. Still work remaining to debug some misc bugs. Made changes to remove all compiler warnings
2020-08-23 Reworked main state machine to be cleaner
2020-08-23 Compensated the temperature sensor output reading based on the latest measured Vdd voltage
2020-08-23 Added decimation to temp reading to make it less noisey
2020-08-23 Lowered SCLK speed and changed word size from 4bits to 8 bits
2020-08-24 Added two new script info registers - line counter, and error status register
2020-08-24 Added doxygen style comment blocks for all functions
2020-08-24 Updated doxygen
2020-08-24 Made it so VREFINT is sampled prior to temp sensor. This prevents issue where TEMP warning is set in STATUS on startup, due to Vdd register being zero when first temp sensor value is calibrated
2020-09-06 Renamed USB_CONFIG to CLI_CONFIG
2020-09-06 Continued SD card data logging implementation. Script file load now working, program throws error creating result text file however
2020-09-16 Added critical section to buf dequeue to prevent potential issues if interrupted by IRQ
2020-09-21 Added support for PPS input signals at 1Hz, 10Hz, 100Hz, 1KHz
2020-09-21 Updated bit definitions for DIO_INPUT_CONFIG
2020-09-27 Reduced ADC clock freq by 50%, increased temp sensor averaging
2020-09-28 Moved disable data capture to main loop, changed it so enable/disable only occurs on write to addr 0
2020-09-28 Changed delay microseconds function to reset DWT timer
2020-09-28 Made some tweaks to the capture enable/disable process
2020-09-30 Switch spi timeout to use HAL systick
2020-10-01 Fixed issue in SD card disk I/O driver causing buffer overflow by 1 byte
2020-10-01 Reverted so output file is opened in append mode. Fixed bug in SD tx handler
2020-10-01 Updated comments and some of the CLI messages. Added new echo command to enable/disable CLI echo for USB
2020-10-01 Fixed formatting
2020-10-01 Fixed some missing function documentation, updated header file to exclude functions from doxygen output
2020-10-01 Updated docs
2020-10-01 Updated timing meaurement, fixed small issue with factory reset time measure function
2020-10-04 Updated documentation for new commands
2020-10-05 Updated CLI docs and help message
2020-10-05 Reworded help message somewhat
2020-10-05 Made CLI tx handlers return for count of 0, fixed issue where two newlines could be inadvertently inserted
2020-10-09 Added cnt read alias command
2020-10-09 Added iamge for CLI cnt command
2020-10-09 Updated the USB CLI description document
2020-10-09 Added a link to the tutorial in the USB_CLI document
2020-10-09 Added the buffer count read command and added the watermark setting to the cli tutorial
2020-10-09 Started working on bootloader jump function
2020-10-09 Created python file for wrapper around CLI
2020-10-11 Added command bit to automatically set the watermark interrupt level
2020-10-12 Changed scr0 -> btn config
2020-10-17 Tweaked some register descriptions
2020-10-17 Got python api working at a base level
2020-10-17 Started to populate example
2020-10-17 Fleshed out example. Seems to be very performanced limited compared to something like tera-term. Will have to investigate more clever readline implementation
2020-10-17 Added readme for python lib
2020-10-18 Renamed folder, added link to top level readme
2020-10-18 Tweaked python lib
2020-10-18 Stop stream now blocks until stream thread exits. Added getters for temp/voltage and updated examples
2020-10-18 Added image showing windows run for example program
2020-10-20 Started working on figuring out how to force USB re-enum on the PC side
2020-10-22 Added name to files, added test file
2020-10-22 Continued test implementation
2020-10-24 Some pretty major changes here. I added a new feature which allows the buffer board to generate an internal sync clock that can be passed to IMU, or used as buffered capture trigger for testing. Deci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
2020-10-24 Fixed checksum calculation
2020-10-24 Added volatile page 252 for future dev work
2020-10-24 Added page 252 description
2020-10-25 Added class to parse out status flags
2020-10-25 Fixes issue with running stream repeatedly. Added stream benchmark program
2020-11-05 Continued work on python library, added stream benchmark function
2020-11-08 Updated example code
2020-11-08 Applied gitignore
2020-11-08 Added test for write data set function. Changed default startup to test file
2020-11-08 Added helper functions to set IMU sclk freq, stall time, and enable burst stream
2020-11-09 Imagine spending literally hours trying to debug an issue and the root cause of the issue is that I am apparently partly dsylexic
2020-11-09 Upreved working version
2020-11-09 Added python data capture flow chart
2020-11-09 Reorganized top level of the repo to make it easier to find things
2020-11-09 Moved example files to their own folder (away from actual interface library)
2020-11-21 Added function to get sn
2021-01-06 Incremented working firmware rev to 1.14
2021-02-23 Added a programming guide.
2021-03-03 Added a document showing the critical mechanical component locations
2021-04-15 Removed ugly goto from the SPI ISR
2021-04-23 Added scale factor for temp and VDD outputs to regmap
2021-04-23 Fixed bug where writing to DIO_INPUT_CONFIG then enabling PPS would inadvertently start a capture early by enabling the IMU DR interrupt
2021-05-11 Removed USB disconnect function - this was not working as expected. Added function to toggle the USB PU pin to trigger a device re-enumeration. This function is always run on startup
2021-05-11 Added buffer timestamp test. This test is relatively basic - it just checks the timestamp behavior in PPS mode
2021-05-11 Marked the user register array volatile
2021-05-11 Regenerated timing doc
2021-06-01 Added guide for setting up the IDE and loading code to hardware
2021-07-22 Moved rev B hardware design files to their own folder. Uploaded initial schematic, layout, and BOM for rev C board
2021-08-24 Modified the user SPI interface to allow for 8 bit transfers. Now interrupts on CS only for burst, otherwise interrupts on Rx data available
2021-08-24 Moved IMU SPI init routine to IMU SPI modules
2021-08-24 Refactored code base to follow a cleaner naming scheme. Now all functions which are part of the public interface of a module are named starting with the module name
2021-08-24 Changed user SPI to operate in byte mode and interrupt once two bytes of data have been received. This improves consistency of behavior. There is still some risk if you transmit an extra byte that th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
2021-08-25 Removed retry which wasnt actually doing anything
2021-08-26 Made some tweaks to the burst setup process. Now, when a burst read is first requested, the software waits for a CS posedge before reconfiguring the SPI for a burst read. This avoids an issue where t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
2021-08-26 Corrected buffer output registers being flagged as signed
2021-08-26 Added check of burst checksum to the 49x test. Set decimate to 0
2021-08-30 Cleaned up the burst handler to fix issue when exiting burst mode
2021-09-09 Corrected for comment spacing

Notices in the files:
Core/Src/dio.c:
Copyright (c) Analog Devices Inc, 2020
All Rights Reserved.
parts and their libraries:
SparkFun-Capacitors: Licensing: Creative Commons ShareAlike 4.0 International - https://creativecommons.org/licenses/by-sa/4.0
tag-connect: ©2009 ROFA.cz - modified and updated by Robert Darlington ‹rdarlington@gmail.com›
